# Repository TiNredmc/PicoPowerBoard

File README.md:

# PicoPowerBoard
PicoPower! Simple but yet powerful. the LITTLE TINY development board based on STM8L151F3 mcu

BOMs
=

1. AMS-1117 3v3 x1 // Whatever to 3.3volt DC regulator IC
2. capacitor SMD 0603 100nF x2
3. capacitor SMD 0603 1uF x1
4. CH330 x1 // Super Small USB to Serial. The 1/2 size compare to CH340
5. Pinheader 1x10 x2
6. Push button SMD right angle 
7. STM8L151F3U6 x1
8. MINI usb B female x1
9. PCB from OSHpark (Don't need 2oz copper). : https://oshpark.com/shared_projects/AjHUwVK9

Photos
=

Coming soon.

Design Flaws is in each folder 
=

# Help Me Imporve !

This project is purely Open Source. Help me make it better. Build it your own !

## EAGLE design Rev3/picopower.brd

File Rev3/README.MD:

# Rev3 is out after I left this project untouch for a while(?)

Improvement 
= 

- Better Schematic layout.
- Better Board layout.
- Move CH330N to back side of the board.
- Using smaller reset button.
- removed unnecessary bypass caps.
- USB2.0 Diff pair lenght match and proper routing.

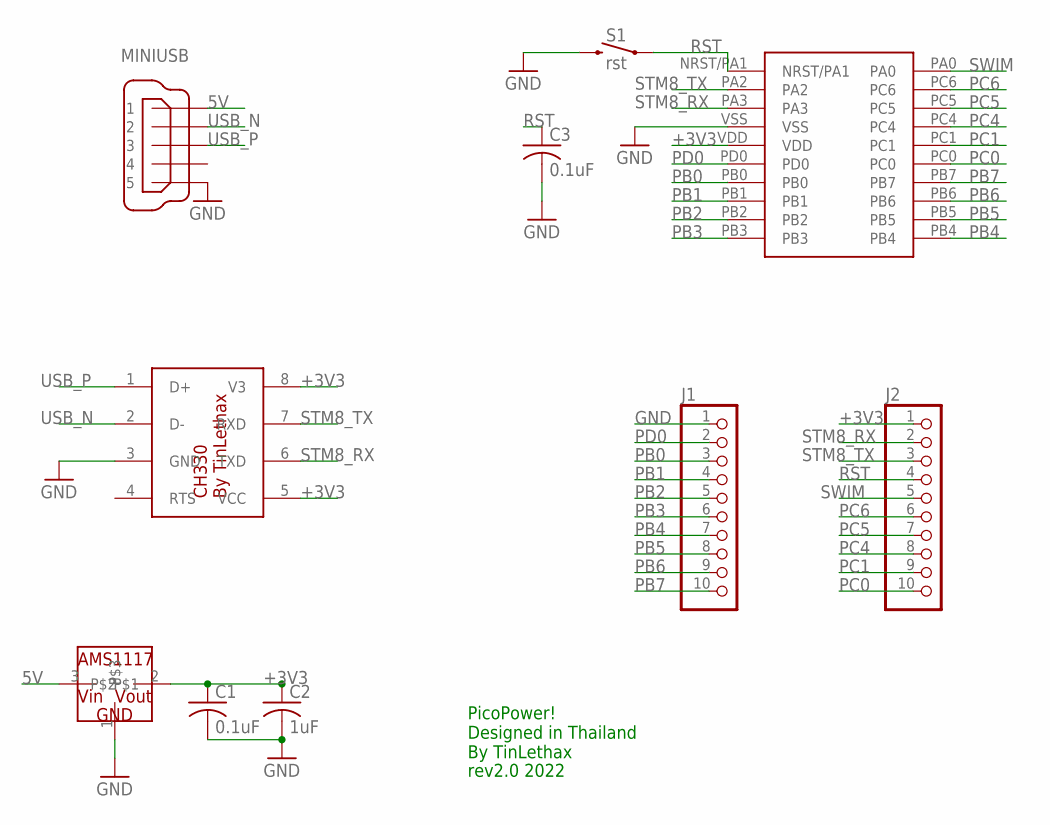
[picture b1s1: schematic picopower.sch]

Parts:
C1, C3: 0.1uF; C0603K
C2: 1uF; C0603K
IC1: STM8L151F3; UFQFPN-20
IC2: CH330; SOIC127P600X150-8N
IC3: AMS1117; SOT223
J1, J2: PINHD-1X10; 1X10-BIG
MINIUSB: MINI-USB-UX60A-MB-5ST; UX60A-MB-5ST
S1: rst; TACTILE_SWITCH_SMD_RIGHT_ANGLE

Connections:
5V: IC3.3, MINIUSB.1
+3V3: C1.1, C2.1, IC1.VDD, IC2.5 (VCC), IC2.8 (V3), IC3.2, J2.1
GND: C1.2, C2.2, C3.2, IC1.VSS, IC2.3 (GND), IC3.1, J1.1, MINIUSB.5, S1.2
PB0: IC1.PB0, J1.3
PB1: IC1.PB1, J1.4
PB2: IC1.PB2, J1.5
PB3: IC1.PB3, J1.6
PB4: IC1.PB4, J1.7
PB5: IC1.PB5, J1.8
PB6: IC1.PB6, J1.9
PB7: IC1.PB7, J1.10
PC0: IC1.PC0, J2.10
PC1: IC1.PC1, J2.9
PC4: IC1.PC4, J2.8
PC5: IC1.PC5, J2.7
PC6: IC1.PC6, J2.6
PD0: IC1.PD0, J1.2
RST: C3.1, IC1.NRST/PA1, J2.4, S1.1
STM8_RX: IC1.PA3, IC2.6 (TXD), J2.2
STM8_TX: IC1.PA2, IC2.7 (RXD), J2.3
SWIM: IC1.PA0, J2.5
USB_N: IC2.2 (D-), MINIUSB.2
USB_P: IC2.1 (D+), MINIUSB.3

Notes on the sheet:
PicoPower! Designed in Thailand By TinLethax
rev2.0 2022

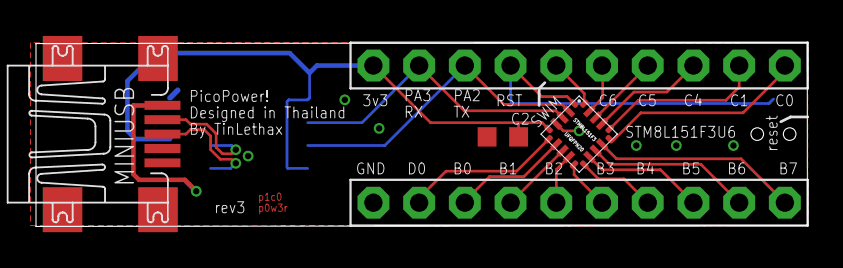
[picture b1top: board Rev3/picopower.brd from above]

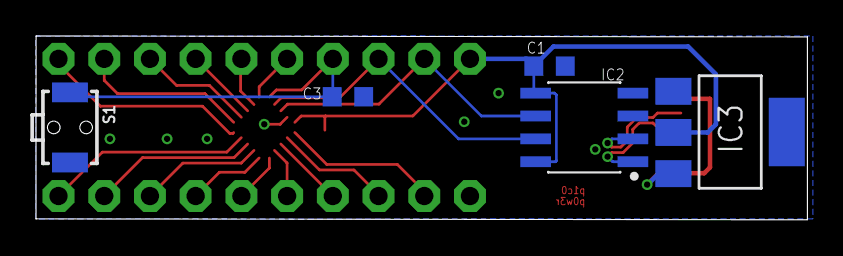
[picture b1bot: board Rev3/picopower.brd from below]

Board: 2 copper layers, 42.9 x 10.2 mm, 10 parts (5 on the bottom side), 23 nets.

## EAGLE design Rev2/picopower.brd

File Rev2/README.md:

# Help Me Improve !

This project is purely Open Source. Grep my design / Make it better / And sell them to me xD (Just kidding).

# Design Flaws (Might be more But this is what I found) 

Yet to be found

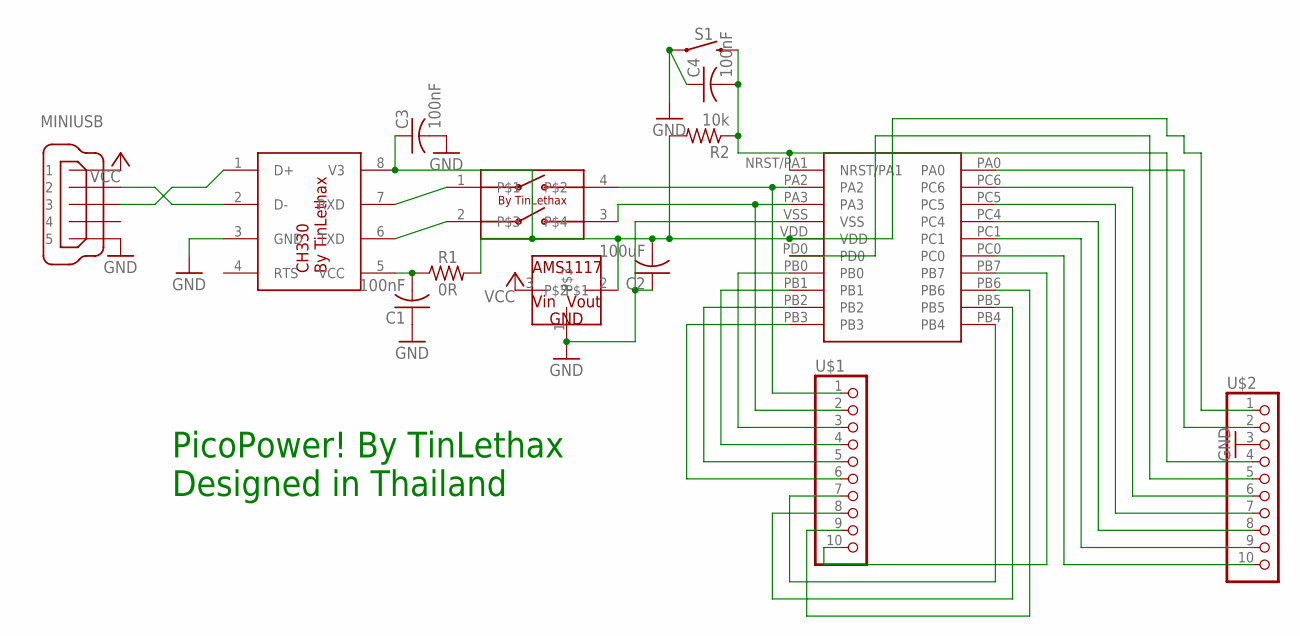
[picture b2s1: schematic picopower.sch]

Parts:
2DIP: 2DIPSWITCH; SOIC127P835X230-4N
C1, C3, C4: 100nF; C0603K
C2: 100uF; C0603K
CH330: CH330; SOIC127P600X150-8N
MINIUSB: MINI-USB-UX60A-MB-5ST; UX60A-MB-5ST
R1: 0R; R0603
R2: 10k; R0603
S1: MOMENTARY-SWITCH-SPST-SMD-6.0X3.5MM; TACTILE_SWITCH_SMD_6.0X3.5MM
STM8L: STM8L151F3; UFQFPN-20
U$1, U$2: PINHD-1X10; 1X10-BIG
U$3: AMS1117; SOT223

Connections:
GND: C1.1, C2.1, C3.2, C4.1, CH330.3 (GND), MINIUSB.5, S1.1, STM8L.VSS, U$2.3, U$3.1
unnamed: 2DIP.1, CH330.7 (RXD)
unnamed: 2DIP.2, CH330.6 (TXD)
unnamed: 2DIP.4, STM8L.PA2, U$1.1
unnamed: 2DIP.3, STM8L.PA3, U$1.2
unnamed: C1.2, CH330.5 (VCC), R1.1
unnamed: C2.2, C3.1, CH330.8 (V3), R1.2, R2.2, STM8L.VDD, U$2.1, U$3.2
unnamed: STM8L.PB0, U$1.3
unnamed: STM8L.PB1, U$1.4
unnamed: STM8L.PB2, U$1.5
unnamed: STM8L.PB3, U$1.6
unnamed: STM8L.PB4, U$1.7
unnamed: STM8L.PB5, U$1.8
unnamed: STM8L.PB6, U$1.9
unnamed: STM8L.PB7, U$1.10
unnamed: STM8L.PC0, U$2.10
unnamed: STM8L.PC1, U$2.9
unnamed: STM8L.PC4, U$2.8
unnamed: STM8L.PC5, U$2.7
unnamed: STM8L.PC6, U$2.6
unnamed: CH330.2 (D-), MINIUSB.2
unnamed: C4.2, R2.1, S1.2, STM8L.NRST/PA1, U$2.4
unnamed: STM8L.PA0, U$2.2
unnamed: STM8L.PD0, U$2.5
unnamed: CH330.1 (D+), MINIUSB.3
VCC: MINIUSB.1, U$3.3

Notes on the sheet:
PicoPower! By TinLethax Designed in Thailand

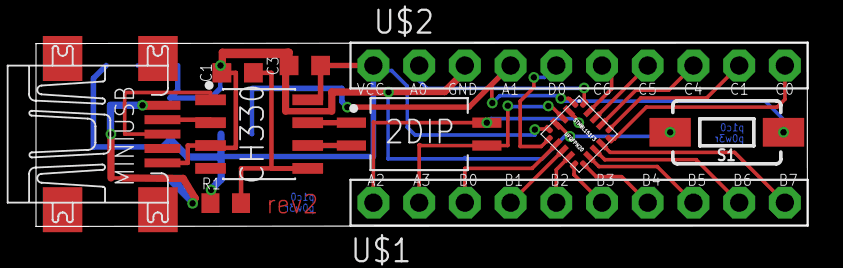
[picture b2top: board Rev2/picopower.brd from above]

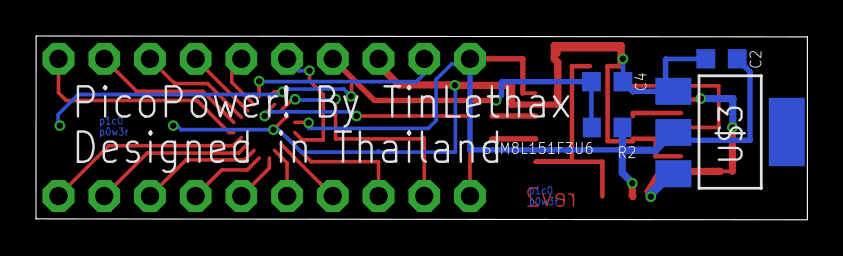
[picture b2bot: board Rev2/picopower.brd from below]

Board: 2 copper layers, 42.9 x 10.2 mm, 14 parts (4 on the bottom side), 26 nets.

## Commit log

2020-03-18 Help Me Improve
2020-03-18 rev0 schematic and board
2020-04-10 rev1 schematic and board
2020-04-10 Update OSHpark link to the rev1 Board
2020-05-19 Update link to rev1.1 PCB
2020-05-19 rev1.1 board
2020-05-28 update PCB link to rev2 board
2020-05-28 typo corrected + flaw
2020-05-28 typo...
2020-05-28 Board and Schematic file
2022-07-03 Added rev3 readme
2022-07-03 Added Rev3 board and Rev2 schematic
2022-07-03 Updated OSHpark link and BOMs

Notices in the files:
parts and their libraries:
SparkFun-Switches: Licensing: Creative Commons ShareAlike 4.0 International - https://creativecommons.org/licenses/by-sa/4.0
